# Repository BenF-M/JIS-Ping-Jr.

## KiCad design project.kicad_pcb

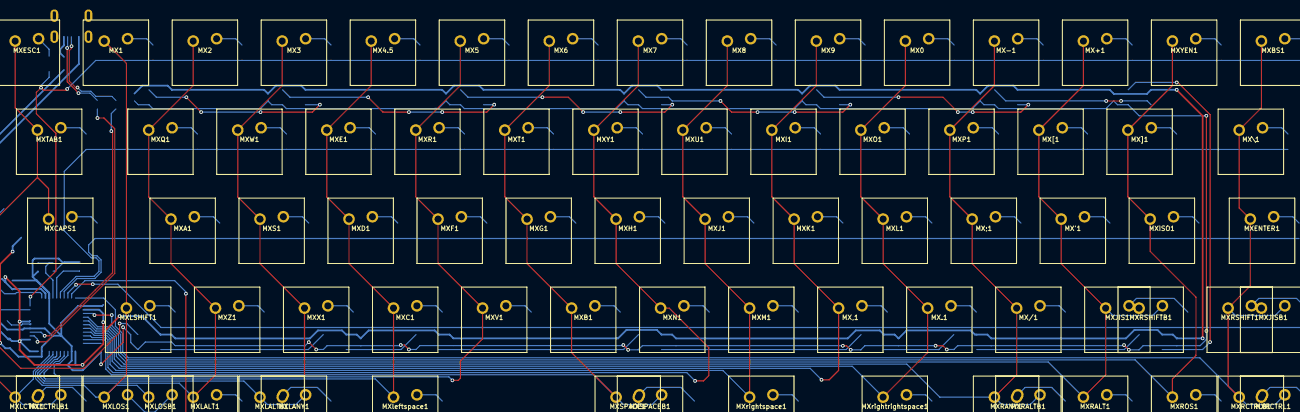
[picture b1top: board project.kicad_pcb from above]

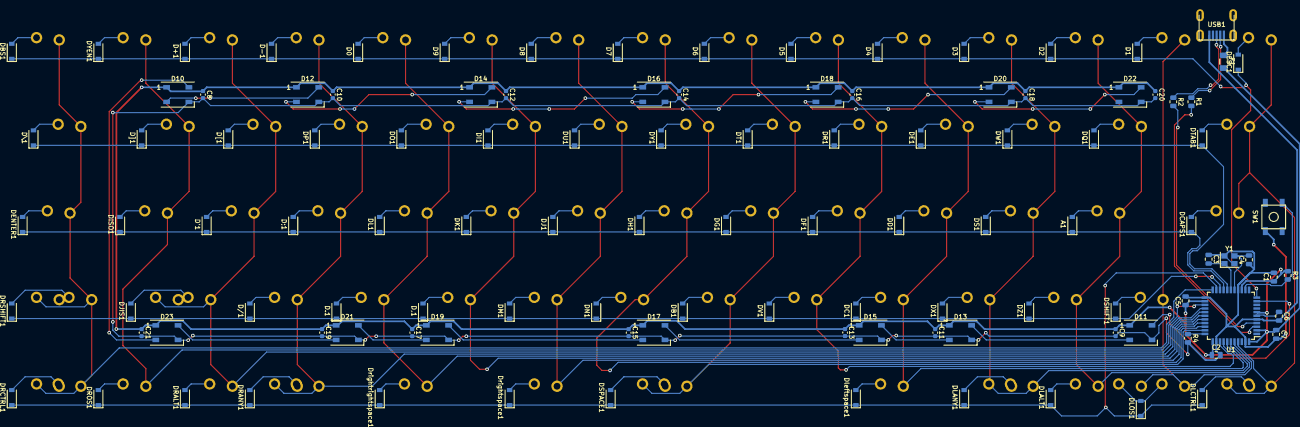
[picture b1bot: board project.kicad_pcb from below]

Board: 2 copper layers, 188 parts (112 on the bottom side), 114 nets.

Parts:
A1: D_Small; D_SOD-123
C1, C2, C5: 0.1uF; C_0805_2012Metric
C3, C4: 22pF; C_0805_2012Metric
C6: 1uF; C_0805_2012Metric
C7: 10uF; C_0805_2012Metric
C8, C9, C10, C11, C12, C13, C14, C15, C16, C17, C18, C19, C20, C21: C_Small; C_0603_1608Metric
D0, D1, D2, D3, D4, D5, D6, D7, D8, D9, D.1: D_Small; D_SOD-123
D10, D11, D12, D13, D14, D15, D16, D17, D18, D19, D20, D21, D22, D23: WS2812B; LED_WS2812B_PLCC4_5.0x5.0mm_P3.2mm
D'1: D_Small; D_SOD-123
D+1: D_Small; D_SOD-123
D,1: D_Small; D_SOD-123
D-1: D_Small; D_SOD-123
D/1: D_Small; D_SOD-123
D;1: D_Small; D_SOD-123
DB1: D_Small; D_SOD-123
DBS1: D_Small; D_SOD-123
DC1: D_Small; D_SOD-123
DCAPS1: D_Small; D_SOD-123
DD1: D_Small; D_SOD-123
DE1: D_Small; D_SOD-123
DENTER1: D_Small; D_SOD-123
DESC1: D_Small; D_SOD-123
DF1: D_Small; D_SOD-123
DG1: D_Small; D_SOD-123
DH1: D_Small; D_SOD-123
DI1: D_Small; D_SOD-123
DISO1: D_Small; D_SOD-123
DJ1: D_Small; D_SOD-123
DJIS1: D_Small; D_SOD-123
DK1: D_Small; D_SOD-123
DL1: D_Small; D_SOD-123
DLALT1: D_Small; D_SOD-123
DLANY1: D_Small; D_SOD-123
DLCTRL1: D_Small; D_SOD-123
DLOS1: D_Small; D_SOD-123
DM1: D_Small; D_SOD-123
DN1: D_Small; D_SOD-123
DO1: D_Small; D_SOD-123
DP1: D_Small; D_SOD-123
DQ1: D_Small; D_SOD-123
DR1: D_Small; D_SOD-123
DRALT1: D_Small; D_SOD-123
DRANY1: D_Small; D_SOD-123
DRCTRL1: D_Small; D_SOD-123
DROS1: D_Small; D_SOD-123
DRSHIFT1: D_Small; D_SOD-123
DS1: D_Small; D_SOD-123
DSHIFT1: D_Small; D_SOD-123
DSPACE1: D_Small; D_SOD-123
DT1: D_Small; D_SOD-123
DTAB1: D_Small; D_SOD-123
DU1: D_Small; D_SOD-123
DV1: D_Small; D_SOD-123
DW1: D_Small; D_SOD-123
DX1: D_Small; D_SOD-123
DY1: D_Small; D_SOD-123
DYEN1: D_Small; D_SOD-123
DZ1: D_Small; D_SOD-123
D[1: D_Small; D_SOD-123
D\1: D_Small; D_SOD-123
D]1: D_Small; D_SOD-123
Dleftspace1: D_Small; D_SOD-123
Drightrightspace1: D_Small; D_SOD-123
Drightspace1: D_Small; D_SOD-123
F1: 500mA; Fuse_1206_3216Metric
MX0, MX1, MX2, MX3, MX4.5, MX5, MX6, MX7, MX8, MX9, MX.1: MX-NoLED; skccWithborder
MX'1: MX-NoLED; skccWithborder
MX+1: MX-NoLED; skccWithborder
MX,1: MX-NoLED; skccWithborder
MX-1: MX-NoLED; skccWithborder
MX/1: MX-NoLED; skccWithborder
MX;1: MX-NoLED; skccWithborder
MXA1: MX-NoLED; skccWithborder
MXB1: MX-NoLED; skccWithborder
MXBS1: MX-NoLED; skccWithborder
MXC1: MX-NoLED; skccWithborder
MXCAPS1: MX-NoLED; skcc1.75
MXD1: MX-NoLED; skccWithborder
MXE1: MX-NoLED; skccWithborder
MXENTER1: MX-NoLED; skcc1.25
MXESC1: MX-NoLED; skccWithborder
MXF1: MX-NoLED; skccWithborder
MXG1: MX-NoLED; skccWithborder
MXH1: MX-NoLED; skccWithborder
MXI1: MX-NoLED; skccWithborder
MXISO1: MX-NoLED; skccWithborder
MXJ1: MX-NoLED; skccWithborder
MXJIS1: MX-NoLED; skccWithborder
MXJISB1: MX-NoLED; skccWithborder
MXK1: MX-NoLED; skccWithborder
MXL1: MX-NoLED; skccWithborder
MXLALT1: MX-NoLED; skccWithborder
MXLALTB1: MX-NoLED; skcc1.5
MXLANY1: MX-NoLED; skccWithborder
MXLCTRL1: MX-NoLED; skccWithborder
MXLCTRLB1: MX-NoLED; skcc1.5
MXLOS1: MX-NoLED; skccWithborder
MXLOSB1: MX-NoLED; skccWithborder
MXLSHIFT1: MX-NoLED; skccWithborder
MXM1: MX-NoLED; skccWithborder
MXN1: MX-NoLED; skccWithborder
MXO1: MX-NoLED; skccWithborder
MXP1: MX-NoLED; skccWithborder
MXQ1: MX-NoLED; skccWithborder
MXR1: MX-NoLED; skccWithborder
MXRALT1: MX-NoLED; skccWithborder
MXRALTB1: MX-NoLED; skcc1.5
MXRANY1: MX-NoLED; skccWithborder
MXRCTRL1: MX-NoLED; skccWithborder
MXRCTRLB1: MX-NoLED; skcc1.5
MXROS1: MX-NoLED; skccWithborder
MXRSHIFT1: MX-NoLED; skcc1.75
MXRSHIFTB1: MX-NoLED; skcc1.75
MXS1: MX-NoLED; skccWithborder
MXSPACE1: MX-NoLED; skcc1.5
MXSPACEB1: MX-NoLED; skcc7
MXT1: MX-NoLED; skccWithborder
MXTAB1: MX-NoLED; skcc1.5
MXU1: MX-NoLED; skccWithborder
MXV1: MX-NoLED; skccWithborder
MXW1: MX-NoLED; skccWithborder
MXX1: MX-NoLED; skccWithborder
MXY1: MX-NoLED; skccWithborder
MXYEN1: MX-NoLED; skccWithborder
MXZ1: MX-NoLED; skccWithborder
MX[1: MX-NoLED; skccWithborder
MX\1: MX-NoLED; skcc1.5
MX]1: MX-NoLED; skccWithborder
MXleftspace1: MX-NoLED; skcc1.5
MXrightrightspace1: MX-NoLED; skcc1.5
MXrightspace1: MX-NoLED; skcc1.5
R1, R2: 22; R_0805_2012Metric
R3, R4: 10k; R_0805_2012Metric
SW1: SW_Push; SKQG-1155865
U1: ATmega32U4-A; TQFP-44_10x10mm_P0.8mm
USB1: Molex-0548190589
Y1: 16MHz; Crystal_SMD_3225-4Pin_3.2x2.5mm

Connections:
+5V: C1.1, C2.1, C5.1, C7.1, C8.1, C9.1, C10.1, C11.1, C12.1, C13.1, C14.1, C15.1, C16.1, C17.1, C18.1, C19.1, C20.1, C21.1, D10.1 (VDD), D11.1 (VDD), D12.1 (VDD), D13.1 (VDD), D14.1 (VDD), D15.1 (VDD), D16.1 (VDD), D17.1 (VDD), D18.1 (VDD), D19.1 (VDD), D20.1 (VDD), D21.1 (VDD), D22.1 (VDD), D23.1 (VDD), F1.2, R3.1, U1.2 (UVCC), U1.7 (VBUS), U1.14 (VCC), U1.24 (AVCC), U1.34 (VCC), U1.44 (AVCC)
COL0: MXCAPS1.1 (COL), MXESC1.1 (COL), MXLCTRL1.1 (COL), MXLCTRLB1.2 (ROW), MXTAB1.1 (COL), U1.41 (PF0)
COL1: MX1.1 (COL), MXLOS1.1 (COL), MXLOSB1.1 (COL), MXLSHIFT1.1 (COL), U1.40 (PF1)
COL2: MX2.1 (COL), MXA1.1 (COL), MXLALT1.1 (COL), MXQ1.1 (COL), MXZ1.1 (COL), U1.39 (PF4)
COL3: MX3.1 (COL), MXLALTB1.1 (COL), MXLANY1.2 (ROW), MXS1.1 (COL), MXW1.1 (COL), MXX1.1 (COL), U1.38 (PF5)
COL4: MX4.5.1 (COL), MXC1.1 (COL), MXD1.1 (COL), MXE1.1 (COL), MXleftspace1.1 (COL), U1.37 (PF6)
COL5: MX5.1 (COL), MXF1.1 (COL), MXR1.1 (COL), MXV1.1 (COL), U1.36 (PF7)
COL6: MX6.1 (COL), MXB1.1 (COL), MXG1.1 (COL), MXSPACE1.1 (COL), MXSPACEB1.2 (ROW), MXT1.1 (COL), U1.32 (PC7)
COL7: MX7.1 (COL), MXH1.1 (COL), MXN1.1 (COL), MXY1.1 (COL), U1.31 (PC6)
COL8: MX8.1 (COL), MXJ1.1 (COL), MXM1.1 (COL), MXU1.1 (COL), MXrightspace1.1 (COL), U1.30 (PB6)
COL9: MX9.1 (COL), MX,1.1 (COL), MXI1.1 (COL), MXK1.1 (COL), U1.29 (PB5)
COL10: MX0.1 (COL), MX.1.1 (COL), MXL1.1 (COL), MXO1.1 (COL), MXrightrightspace1.1 (COL), U1.28 (PB4)
COL11: MX-1.1 (COL), MX/1.1 (COL), MX;1.1 (COL), MXP1.1 (COL), MXRALTB1.2 (ROW), MXRANY1.1 (COL), U1.27 (PD7)
COL12: MX'1.1 (COL), MX+1.1 (COL), MXJIS1.1 (COL), MXRALT1.1 (COL), MXRSHIFTB1.2 (ROW), MX[1.1 (COL), U1.26 (PD6)
COL13: MXISO1.1 (COL), MXROS1.1 (COL), MXYEN1.1 (COL), MX]1.1 (COL), U1.25 (PD4)
COL14: MXBS1.1 (COL), MXENTER1.1 (COL), MXJISB1.2 (ROW), MXRCTRL1.2 (ROW), MXRCTRLB1.1 (COL), MXRSHIFT1.1 (COL), MX\1.1 (COL), U1.22 (PD5)
D+: R2.1, USB1.3 (D+)
D-: R1.1, USB1.4 (D-)
unnamed: C3.2, U1.17 (XTAL1), Y1.1
unnamed: C4.2, U1.16 (XTAL2), Y1.3
unnamed: C6.1, U1.6 (UCAP)
unnamed: D1.2 (A), MX1.2 (ROW)
unnamed: D5.2 (A), MX5.2 (ROW)
unnamed: D6.2 (A), MX6.2 (ROW)
unnamed: D8.2 (A), MX8.2 (ROW)
unnamed: D10.2 (DOUT), D12.4 (DIN)
unnamed: D10.4 (DIN), D23.2 (DOUT)
unnamed: D11.2 (DOUT), D13.4 (DIN)
unnamed: D12.2 (DOUT), D14.4 (DIN)
unnamed: D13.2 (DOUT), D15.4 (DIN)
unnamed: D14.2 (DOUT), D16.4 (DIN)
unnamed: D15.2 (DOUT), D17.4 (DIN)
unnamed: D16.2 (DOUT), D18.4 (DIN)
unnamed: D17.2 (DOUT), D19.4 (DIN)
unnamed: D18.2 (DOUT), D20.4 (DIN)
unnamed: D19.2 (DOUT), D21.4 (DIN)
unnamed: D20.2 (DOUT), D22.4 (DIN)
unnamed: D21.2 (DOUT), D23.4 (DIN)
unnamed: D+1.2 (A), MX+1.2 (ROW)
unnamed: D-1.2 (A), MX-1.2 (ROW)
unnamed: D;1.2 (A), MX;1.2 (ROW)
unnamed: DBS1.2 (A), MXBS1.2 (ROW)
unnamed: DESC1.2 (A), MXESC1.2 (ROW)
unnamed: DF1.2 (A), MXF1.2 (ROW)
unnamed: DJ1.2 (A), MXJ1.2 (ROW)
unnamed: DK1.2 (A), MXK1.2 (ROW)
unnamed: DL1.2 (A), MXL1.2 (ROW)
unnamed: DO1.2 (A), MXO1.2 (ROW)
unnamed: DP1.2 (A), MXP1.2 (ROW)
unnamed: DR1.2 (A), MXR1.2 (ROW)
unnamed: DRANY1.2 (A), MXRALTB1.1 (COL), MXRANY1.2 (ROW)
unnamed: DRCTRL1.2 (A), MXRCTRL1.1 (COL), MXRCTRLB1.2 (ROW)
unnamed: DS1.2 (A), MXS1.2 (ROW)
unnamed: DTAB1.2 (A), MXTAB1.2 (ROW)
unnamed: DW1.2 (A), MXW1.2 (ROW)
unnamed: DYEN1.2 (A), MXYEN1.2 (ROW)
unnamed: Dleftspace1.2 (A), MXleftspace1.2 (ROW)
unnamed: Drightrightspace1.2 (A), MXrightrightspace1.2 (ROW)
unnamed: Drightspace1.2 (A), MXrightspace1.2 (ROW)
unnamed: D0.2 (A), MX0.2 (ROW)
unnamed: D2.2 (A), MX2.2 (ROW)
unnamed: D3.2 (A), MX3.2 (ROW)
unnamed: D4.2 (A), MX4.5.2 (ROW)
unnamed: D7.2 (A), MX7.2 (ROW)
unnamed: D9.2 (A), MX9.2 (ROW)
unnamed: D'1.2 (A), MX'1.2 (ROW)
unnamed: D,1.2 (A), MX,1.2 (ROW)
unnamed: D.1.2 (A), MX.1.2 (ROW)
unnamed: D/1.2 (A), MX/1.2 (ROW)
unnamed: A1.2 (A), MXA1.2 (ROW)
unnamed: DB1.2 (A), MXB1.2 (ROW)
unnamed: DC1.2 (A), MXC1.2 (ROW)
unnamed: DCAPS1.2 (A), MXCAPS1.2 (ROW)
unnamed: DD1.2 (A), MXD1.2 (ROW)
unnamed: DE1.2 (A), MXE1.2 (ROW)
unnamed: DENTER1.2 (A), MXENTER1.2 (ROW)
unnamed: DG1.2 (A), MXG1.2 (ROW)
unnamed: DH1.2 (A), MXH1.2 (ROW)
unnamed: DI1.2 (A), MXI1.2 (ROW)
unnamed: DISO1.2 (A), MXISO1.2 (ROW)
unnamed: DRSHIFT1.2 (A), MXJISB1.1 (COL), MXRSHIFT1.2 (ROW)
unnamed: DLALT1.2 (A), MXLALT1.2 (ROW)
unnamed: DLANY1.2 (A), MXLALTB1.2 (ROW), MXLANY1.1 (COL)
unnamed: DLCTRL1.2 (A), MXLCTRL1.2 (ROW), MXLCTRLB1.1 (COL)
unnamed: DLOS1.2 (A), MXLOS1.2 (ROW), MXLOSB1.2 (ROW)
unnamed: DSHIFT1.2 (A), MXLSHIFT1.2 (ROW)
unnamed: DM1.2 (A), MXM1.2 (ROW)
unnamed: DN1.2 (A), MXN1.2 (ROW)
unnamed: DQ1.2 (A), MXQ1.2 (ROW)
unnamed: DRALT1.2 (A), MXRALT1.2 (ROW)
unnamed: DROS1.2 (A), MXROS1.2 (ROW)
unnamed: DJIS1.2 (A), MXJIS1.2 (ROW), MXRSHIFTB1.1 (COL)
unnamed: DSPACE1.2 (A), MXSPACE1.2 (ROW), MXSPACEB1.1 (COL)
unnamed: DT1.2 (A), MXT1.2 (ROW)
unnamed: DU1.2 (A), MXU1.2 (ROW)
unnamed: DV1.2 (A), MXV1.2 (ROW)
unnamed: DX1.2 (A), MXX1.2 (ROW)
unnamed: DY1.2 (A), MXY1.2 (ROW)
unnamed: DZ1.2 (A), MXZ1.2 (ROW)
unnamed: D[1.2 (A), MX[1.2 (ROW)
unnamed: D\1.2 (A), MX\1.2 (ROW)
unnamed: D]1.2 (A), MX]1.2 (ROW)
unnamed: R1.2, U1.3 (D-)
unnamed: R2.2, U1.4 (D+)
unnamed: R3.2, SW1.2, U1.13 (~RESET)
unnamed: R4.1, U1.33 (~HWB/PE2)
RGB LED: D11.4 (DIN), U1.10 (PB2)
ROW0: D0.1 (K), D1.1 (K), D2.1 (K), D3.1 (K), D4.1 (K), D5.1 (K), D6.1 (K), D7.1 (K), D8.1 (K), D9.1 (K), D+1.1 (K), D-1.1 (K), DBS1.1 (K), DESC1.1 (K), DYEN1.1 (K), U1.11 (PB3)
ROW1: DE1.1 (K), DI1.1 (K), DO1.1 (K), DP1.1 (K), DQ1.1 (K), DR1.1 (K), DT1.1 (K), DTAB1.1 (K), DU1.1 (K), DW1.1 (K), DY1.1 (K), D[1.1 (K), D\1.1 (K), D]1.1 (K), U1.18 (PD0)
ROW2: A1.1 (K), D'1.1 (K), D;1.1 (K), DCAPS1.1 (K), DD1.1 (K), DENTER1.1 (K), DF1.1 (K), DG1.1 (K), DH1.1 (K), DISO1.1 (K), DJ1.1 (K), DK1.1 (K), DL1.1 (K), DS1.1 (K), U1.19 (PD1)
ROW3: D,1.1 (K), D.1.1 (K), D/1.1 (K), DB1.1 (K), DC1.1 (K), DJIS1.1 (K), DM1.1 (K), DN1.1 (K), DRSHIFT1.1 (K), DSHIFT1.1 (K), DV1.1 (K), DX1.1 (K), DZ1.1 (K), U1.20 (PD2)
ROW4: DLALT1.1 (K), DLANY1.1 (K), DLCTRL1.1 (K), DLOS1.1 (K), DRALT1.1 (K), DRANY1.1 (K), DRCTRL1.1 (K), DROS1.1 (K), DSPACE1.1 (K), Dleftspace1.1 (K), Drightrightspace1.1 (K), Drightspace1.1 (K), U1.21 (PD3)
VCC: F1.1, USB1.5 (VBUS)
e: C1.2, C2.2, C3.1, C4.1, C5.2, C6.2, C7.2, C8.2, C9.2, C10.2, C11.2, C12.2, C13.2, C14.2, C15.2, C16.2, C17.2, C18.2, C19.2, C20.2, C21.2, D10.3 (VSS), D11.3 (VSS), D12.3 (VSS), D13.3 (VSS), D14.3 (VSS), D15.3 (VSS), D16.3 (VSS), D17.3 (VSS), D18.3 (VSS), D19.3 (VSS), D20.3 (VSS), D21.3 (VSS), D22.3 (VSS), D23.3 (VSS), R4.2, SW1.1, U1.5 (UGND), U1.15 (GND), U1.23 (GND), U1.35 (GND), U1.43 (GND), USB1.1 (GND), Y1.2, Y1.4

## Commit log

2022-03-23 added ai3's things
2022-03-23 startagain
2022-03-23 controller done
2022-03-23 controller done2
2022-03-24 more additions, missing components
2022-05-18 footprints assigned
2022-05-29 kind of done? no checks or fills
2022-06-14 halfway through leds
2022-06-14 stop here for discontinued rgb
2022-06-23 Please add screw holes, solenoid, and fill zones
